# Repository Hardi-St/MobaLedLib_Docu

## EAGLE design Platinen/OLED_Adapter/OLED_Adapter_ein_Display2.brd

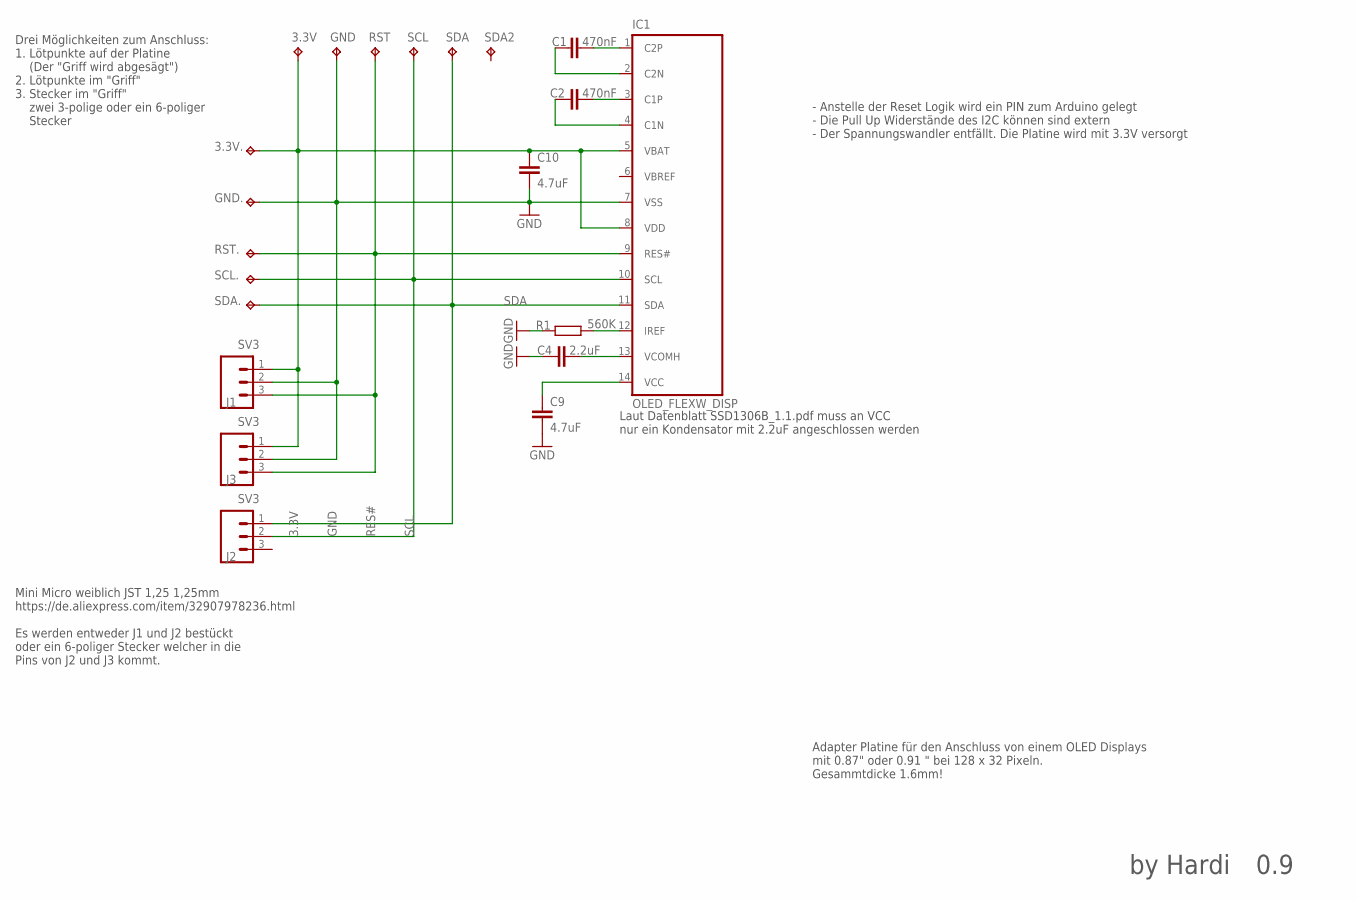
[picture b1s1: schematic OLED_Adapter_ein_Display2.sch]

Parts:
3.3V: 3.3V; TP16SQ
3.3V.: TPTP16SQ; TP16SQ
C1, C2: 470nF; C0603
C4: 2.2uF; C0603
C9, C10: 4.7uF; C0603
GND: GND; TP16R
GND.: TPTP16R; TP16R
IC1: OLED_FLEXW_DISP; OLED_FLEX_W_DISP
J1, J2, J3: SV3; MINI
R1: 560K; R0603
RST: RST; TP16R
RST.: TPTP16R; TP16R
SCL: SCL; TP16R
SCL.: TPTP16R; TP16R
SDA: SDA; TP16R
SDA2: SDA2; TP16R
SDA.: TPTP16R; TP16R

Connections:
3.3V: 3.3V.TP, 3.3V..TP, C10.1, IC1.5 (VBAT), IC1.8 (VDD), J1.1, J3.1
GND: C4.1, C9.2, C10.2, GND.TP, GND..TP, IC1.7 (VSS), J1.2, J3.2, R1.1
unnamed: IC1.12 (IREF), R1.2
unnamed: C1.2, IC1.1 (C2P)
unnamed: C1.1, IC1.2 (C2N)
unnamed: C2.2, IC1.3 (C1P)
unnamed: C2.1, IC1.4 (C1N)
unnamed: C9.1, IC1.14 (VCC)
unnamed: C4.2, IC1.13 (VCOMH)
RES#: IC1.9 (RES#), J1.3, J3.3, RST.TP, RST..TP
SCL: IC1.10 (SCL), J2.2, SCL.TP, SCL..TP
SDA: IC1.11 (SDA), J2.1, SDA.TP, SDA..TP

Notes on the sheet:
Laut Datenblatt SSD1306B_1.1.pdf muss an VCC nur ein Kondensator mit 2.2uF angeschlossen werden
- Anstelle der Reset Logik wird ein PIN zum Arduino gelegt - Die Pull Up Widerstände des I2C können sind extern - Der Spannungswandler entfällt. Die Platine wird mit 3.3V versorgt
Adapter Platine für den Anschluss von einem OLED Displays mit 0.87" oder 0.91 " bei 128 x 32 Pixeln. Gesammtdicke 1.6mm!
0.9
by Hardi
Mini Micro weiblich JST 1,25 1,25mm https://de.aliexpress.com/item/32907978236.html Es werden entweder J1 und J2 bestückt oder ein 6-poliger Stecker welcher in die Pins von J2 und J3 kommt.
Drei Möglichkeiten zum Anschluss: 1. Lötpunkte auf der Platine (Der "Griff wird abgesägt") 2. Lötpunkte im "Griff" 3. Stecker im "Griff" zwei 3-polige oder ein 6-poliger Stecker

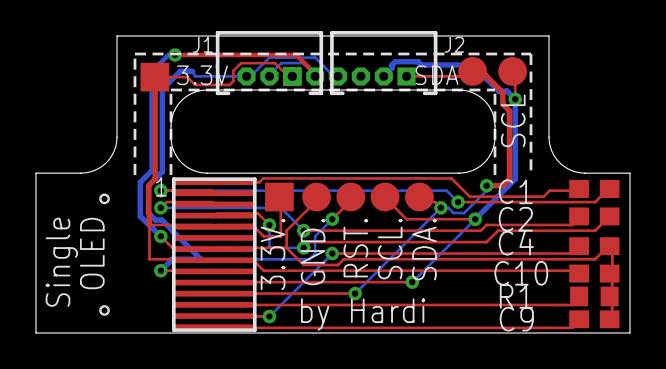
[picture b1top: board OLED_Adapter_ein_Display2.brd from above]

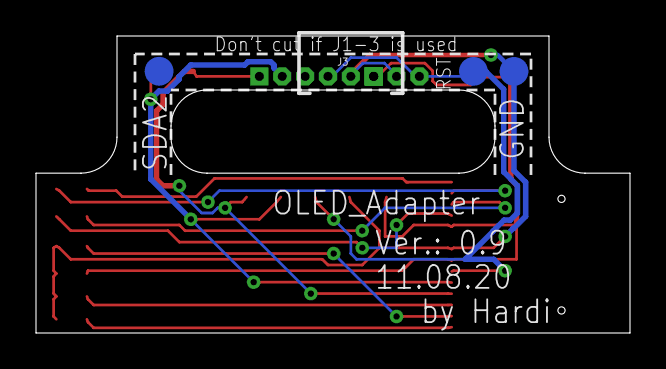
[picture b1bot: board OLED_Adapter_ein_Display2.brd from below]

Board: 2 copper layers, 33.0 x 16.5 mm, 21 parts (4 on the bottom side), 12 nets.

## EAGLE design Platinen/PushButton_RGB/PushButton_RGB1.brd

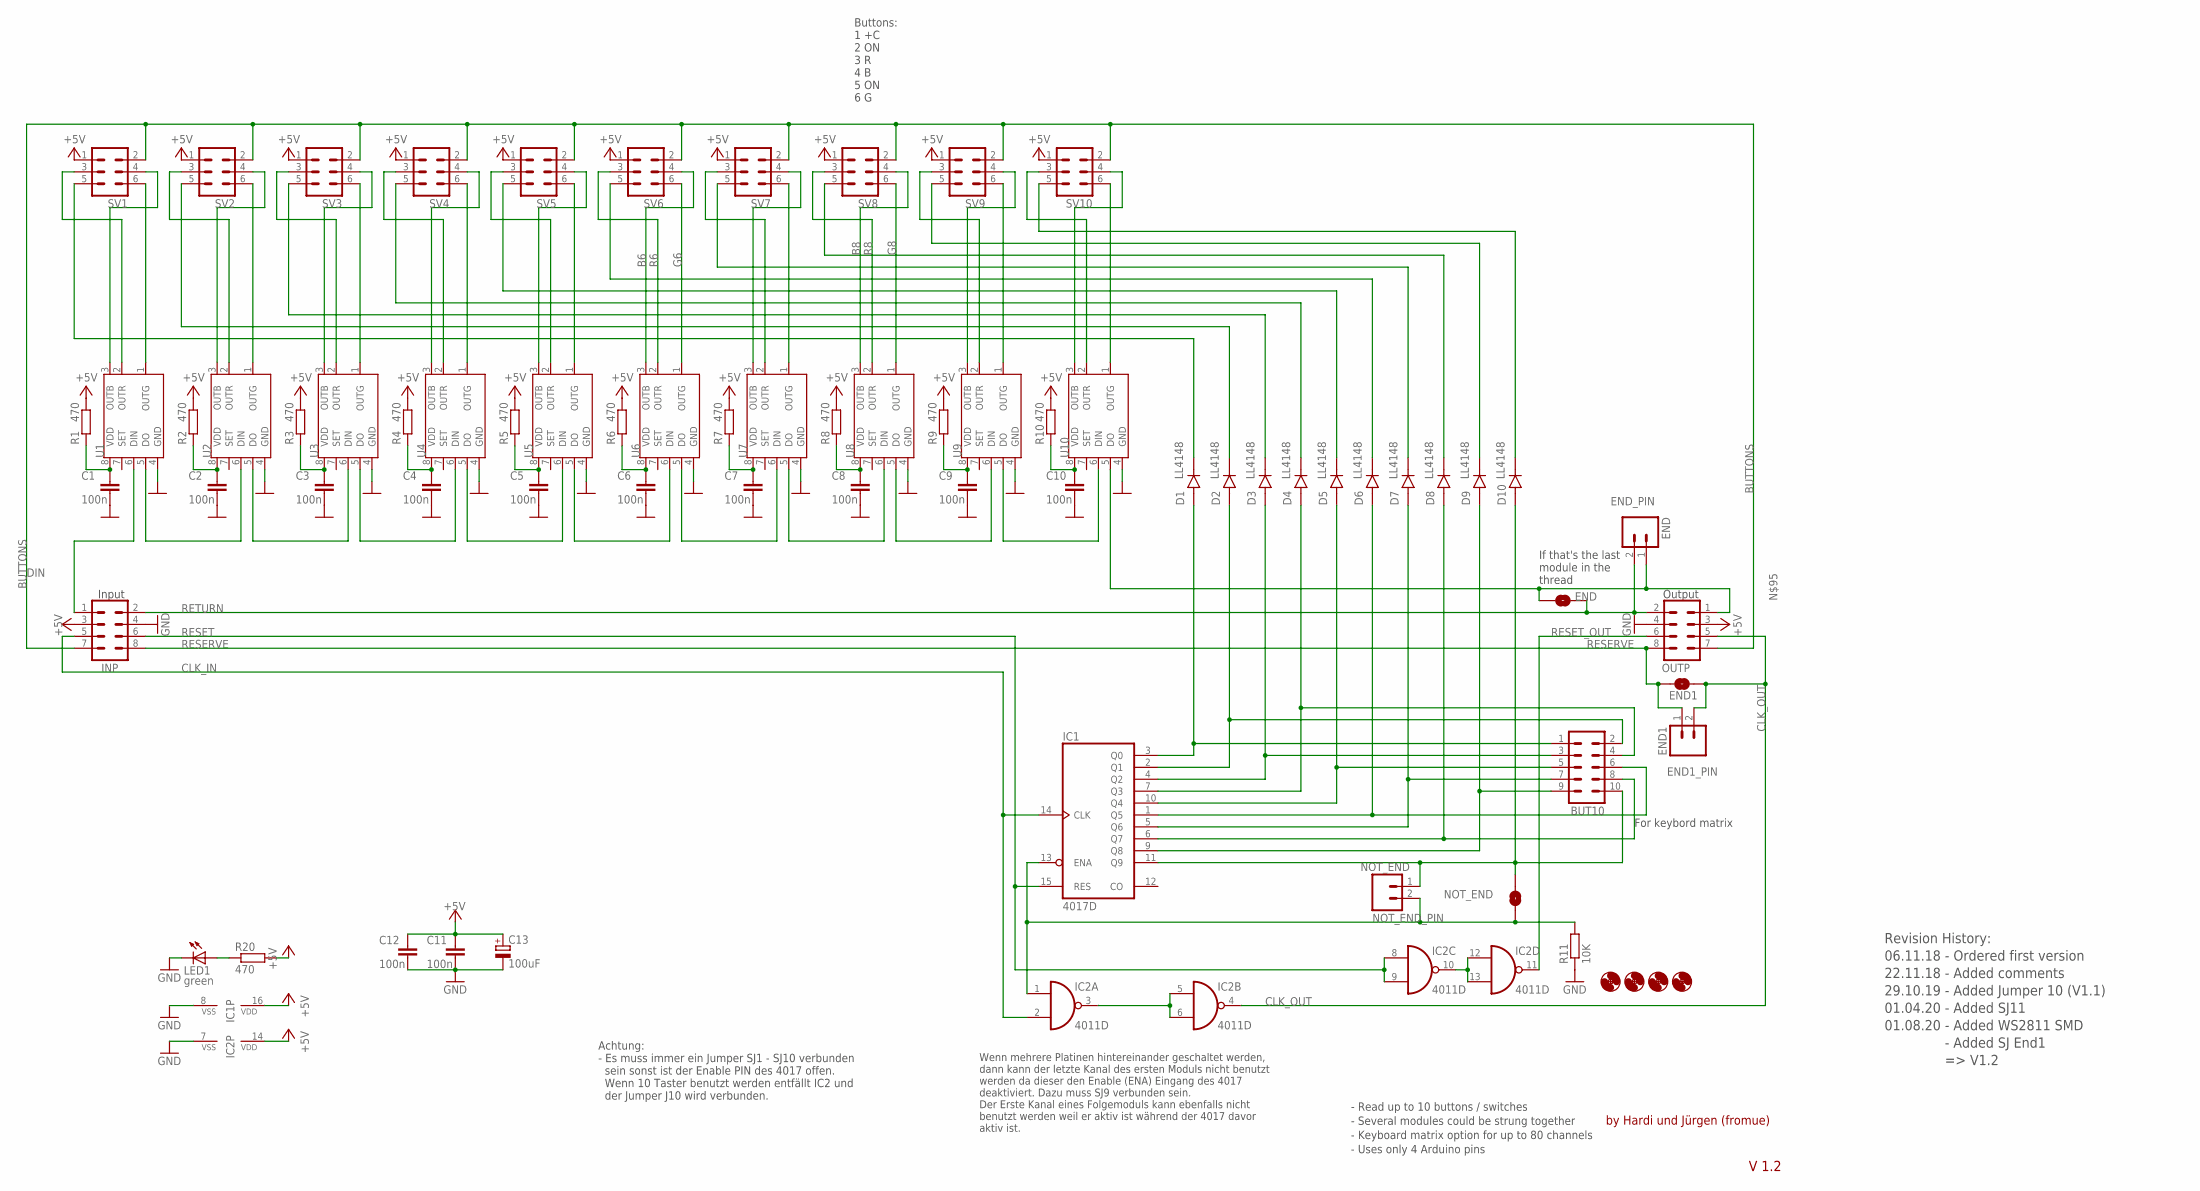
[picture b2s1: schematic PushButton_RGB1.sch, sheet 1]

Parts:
BUT10: CON-HARTING-ML_ML10
C1, C2, C3, C4, C5, C6, C7, C8, C9, C10, C11, C12: 100n; C0603
C13: 100uF; D/7343-31W
D1, D2, D3, D4, D5, D6, D7, D8, D9, D10: LL4148; DIO_LL4148
END, END1: SOLDERJUMPERNO; SJ_2S-NO
END1_PIN: END1; 1X02
END_PIN: END; 1X02
H1, H2, H3: MOUNT-HOLE3.0; 3,0
H4: MOUNT-HOLE2.8; 2,8
IC1: 4017D; SO16
IC2: 4011D; SO14
INP: CON-HARTING-ML_ML08
LED1: green; LED3MM
NOT_END: SOLDERJUMPERNO; SJ_2S-NO
NOT_END_PIN: NOT_END; 1X02
OUTP: CON-HARTING-ML_ML08
R1, R2, R3, R4, R5, R6, R7, R8, R9, R10, R20: 470; R0603
R11: 10K; R0603
SV1, SV2, SV3, SV4, SV5, SV6, SV7, SV8, SV9, SV10: CON-HARTING-ML_ML6
U1, U2, U3, U4, U5, U6, U7, U8, U9, U10: S3PO_MODUL_WS2811_SOUND_MP3-TF-16P_WS2811_AND_ATT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; SOP8

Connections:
+5V: C11.1, C12.1, C13.+, IC1.16 (VDD), IC2.14 (VDD), INP.3, OUTP.3, R1.2, R2.2, R3.2, R4.2, R5.2, R6.2, R7.2, R8.2, R9.2, R10.2, R20.2, SV1.1, SV2.1, SV3.1, SV4.1, SV5.1, SV6.1, SV7.1, SV8.1, SV9.1, SV10.1; also elsewhere on the board
B6: SV6.4, U6.3 (OUTB)
B8: SV8.4, U8.3 (OUTB)
BUTTONS: INP.7, OUTP.7, SV1.2, SV2.2, SV3.2, SV4.2, SV5.2, SV6.2, SV7.2, SV8.2, SV9.2, SV10.2; also elsewhere on the board
CLK_IN: IC1.14 (CLK), IC2.2 (I1), INP.5
CLK_OUT: END1.1, END1_PIN.2, IC2.4 (O), OUTP.5
DIN: INP.1, U1.6 (DIN)
G6: SV6.6, U6.1 (OUTG)
G8: SV8.6, U8.1 (OUTG)
GND: C1.2, C2.2, C3.2, C4.2, C5.2, C6.2, C7.2, C8.2, C9.2, C10.2, C11.2, C12.2, C13.-, IC1.8 (VSS), IC2.7 (VSS), INP.4, LED1.K (C), OUTP.4, R11.1, U1.4 (GND), U2.4 (GND), U3.4 (GND), U4.4 (GND), U5.4 (GND), U6.4 (GND), U7.4 (GND), U8.4 (GND), U9.4 (GND), U10.4 (GND)
unnamed: IC2.3 (O), IC2.5 (I0), IC2.6 (I1)
unnamed: IC1.13 (ENA), IC2.1 (I0), NOT_END.1, NOT_END_PIN.2, R11.2
unnamed: IC2.10 (O), IC2.12 (I0), IC2.13 (I1)
unnamed: BUT10.10, D10.A, IC1.11 (Q9), NOT_END.2, NOT_END_PIN.1
unnamed: C3.1, R3.1, U3.8 (VDD)
unnamed: C6.1, R6.1, U6.8 (VDD)
unnamed: U3.5 (DO), U4.6 (DIN)
unnamed: C4.1, R4.1, U4.8 (VDD)
unnamed: D9.C, SV9.5
unnamed: BUT10.2, D2.A, IC1.2 (Q1)
unnamed: BUT10.3, D3.A, IC1.4 (Q2)
unnamed: BUT10.4, D4.A, IC1.7 (Q3)
unnamed: BUT10.5, D5.A, IC1.10 (Q4)
unnamed: BUT10.6, D6.A, IC1.1 (Q5)
unnamed: BUT10.7, D7.A, IC1.5 (Q6)
unnamed: BUT10.8, D8.A, IC1.6 (Q7)
unnamed: BUT10.9, D9.A, IC1.9 (Q8)
unnamed: SV1.3, U1.2 (OUTR)
unnamed: U4.5 (DO), U5.6 (DIN)
unnamed: LED1.A, R20.1
unnamed: U1.5 (DO), U2.6 (DIN)
unnamed: C5.1, R5.1, U5.8 (VDD)
unnamed: D10.C, SV10.5
unnamed: SV1.4, U1.3 (OUTB)
unnamed: SV1.6, U1.1 (OUTG)
unnamed: BUT10.1, D1.A, IC1.3 (Q0)
unnamed: SV2.4, U2.3 (OUTB)
unnamed: SV2.6, U2.1 (OUTG)
unnamed: SV2.3, U2.2 (OUTR)
unnamed: SV3.4, U3.3 (OUTB)
unnamed: SV3.6, U3.1 (OUTG)
unnamed: SV3.3, U3.2 (OUTR)
unnamed: C1.1, R1.1, U1.8 (VDD)
unnamed: C2.1, R2.1, U2.8 (VDD)
unnamed: U6.5 (DO), U7.6 (DIN)
unnamed: U2.5 (DO), U3.6 (DIN)
unnamed: U5.5 (DO), U6.6 (DIN)
unnamed: C7.1, R7.1, U7.8 (VDD)
unnamed: U7.5 (DO), U8.6 (DIN)
unnamed: C8.1, R8.1, U8.8 (VDD)
unnamed: SV4.4, U4.3 (OUTB)
unnamed: SV4.6, U4.1 (OUTG)
unnamed: U8.5 (DO), U9.6 (DIN)
unnamed: C9.1, R9.1, U9.8 (VDD)
unnamed: SV4.3, U4.2 (OUTR)
unnamed: U9.5 (DO), U10.6 (DIN)
unnamed: C10.1, R10.1, U10.8 (VDD)
unnamed: END.2, END_PIN.1, OUTP.1, U10.5 (DO)
unnamed: SV5.4, U5.3 (OUTB)
unnamed: SV5.6, U5.1 (OUTG)
unnamed: SV5.3, U5.2 (OUTR)
unnamed: SV7.4, U7.3 (OUTB)
unnamed: SV7.6, U7.1 (OUTG)
unnamed: SV7.3, U7.2 (OUTR)
unnamed: SV9.4, U9.3 (OUTB)
unnamed: SV9.6, U9.1 (OUTG)
unnamed: SV9.3, U9.2 (OUTR)
unnamed: SV10.4, U10.3 (OUTB)
unnamed: SV10.6, U10.1 (OUTG)
unnamed: SV10.3, U10.2 (OUTR)
unnamed: D1.C, SV1.5
unnamed: D2.C, SV2.5
unnamed: D3.C, SV3.5
unnamed: D4.C, SV4.5
unnamed: D5.C, SV5.5
unnamed: D6.C, SV6.5
unnamed: D7.C, SV7.5
unnamed: D8.C, SV8.5
R6: SV6.3, U6.2 (OUTR)
R8: SV8.3, U8.2 (OUTR)
RESERVE: END1.2, END1_PIN.1, INP.8, OUTP.8
RESET: IC1.15 (RES), IC2.8 (I0), IC2.9 (I1), INP.6
RESET_OUT: IC2.11 (O), OUTP.6
RETURN: END.1, END_PIN.2, INP.2, OUTP.2

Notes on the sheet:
Input
Output
by Hardi und Jürgen (fromue)
- Read up to 10 buttons / switches - Several modules could be strung together - Keyboard matrix option for up to 80 channels - Uses only 4 Arduino pins
For keybord matrix
If that's the last module in the thread
Achtung: - Es muss immer ein Jumper SJ1 - SJ10 verbunden sein sonst ist der Enable PIN des 4017 offen. Wenn 10 Taster benutzt werden entfällt IC2 und der Jumper J10 wird verbunden.
Wenn mehrere Platinen hintereinander geschaltet werden, dann kann der letzte Kanal des ersten Moduls nicht benutzt werden da dieser den Enable (ENA) Eingang des 4017 deaktiviert. Dazu muss SJ9 verbunden sein. Der Erste Kanal eines Folgemoduls kann ebenfalls nicht benutzt werden weil er aktiv ist wä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
Revision History: 06.11.18 - Ordered first version 22.11.18 - Added comments 29.10.19 - Added Jumper 10 (V1.1) 01.04.20 - Added SJ11 01.08.20 - Added WS2811 SMD - Added SJ End1 => V1.2
V 1.2
Buttons: 1 +C 2 ON 3 R 4 B 5 ON 6 G

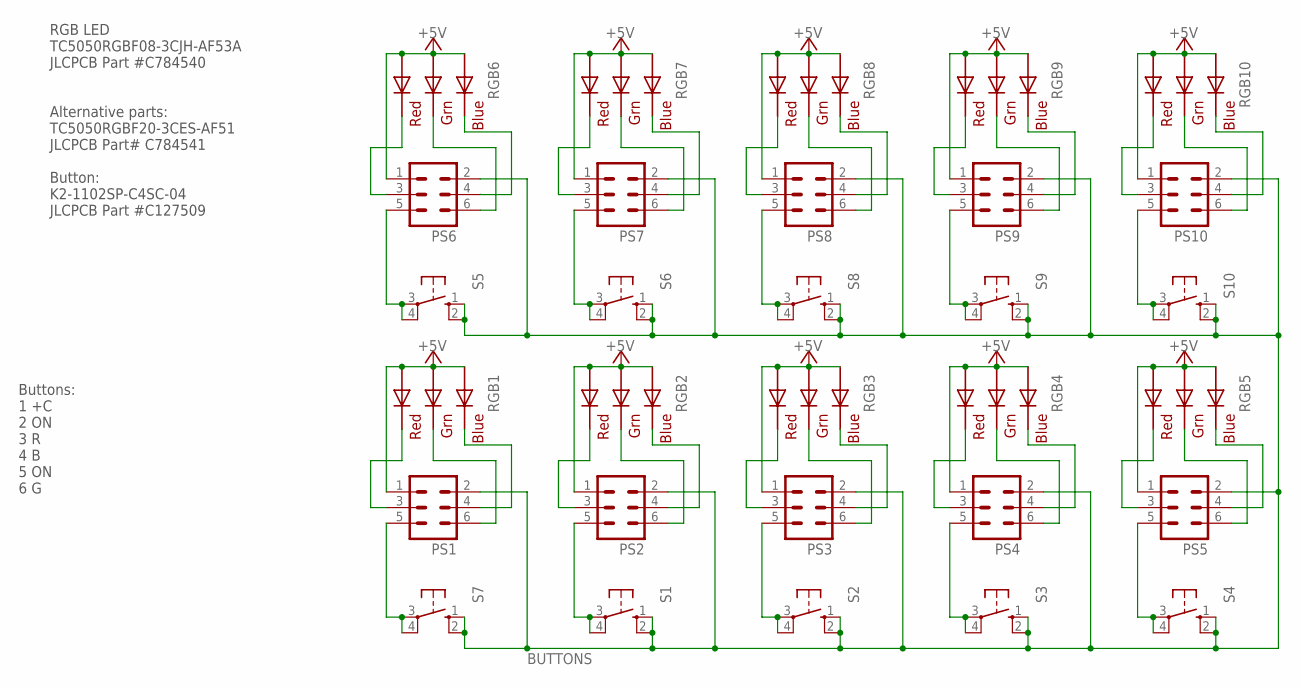
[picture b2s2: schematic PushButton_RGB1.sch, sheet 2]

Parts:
PS1, PS2, PS3, PS4, PS5, PS6, PS7, PS8, PS9, PS10: CON-HARTING-ML_ML6BKL10120958; BKL10120958_MIRROR
RGB1, RGB2, RGB3, RGB4, RGB5, RGB6, RGB7, RGB8, RGB9, RGB10: RGBLED5050
S1, S2, S3, S4, S5, S6, S7, S8, S9, S10: 10-XXB3F-10XX_SMD; B3F-10XX_SMD

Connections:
+5V: PS1.1, PS2.1, PS3.1, PS4.1, PS5.1, PS6.1, PS7.1, PS8.1, PS9.1, PS10.1, RGB1.1 (GREEN_A), RGB1.2 (RED_A), RGB1.3 (BLUE_A), RGB2.1 (GREEN_A), RGB2.2 (RED_A), RGB2.3 (BLUE_A), RGB3.1 (GREEN_A), RGB3.2 (RED_A), RGB3.3 (BLUE_A), RGB4.1 (GREEN_A), RGB4.2 (RED_A), RGB4.3 (BLUE_A), RGB5.1 (GREEN_A), RGB5.2 (RED_A), RGB5.3 (BLUE_A), RGB6.1 (GREEN_A), RGB6.2 (RED_A), RGB6.3 (BLUE_A), RGB7.1 (GREEN_A), RGB7.2 (RED_A), RGB7.3 (BLUE_A), RGB8.1 (GREEN_A), RGB8.2 (RED_A), RGB8.3 (BLUE_A), RGB9.1 (GREEN_A), RGB9.2 (RED_A), RGB9.3 (BLUE_A), RGB10.1 (GREEN_A), RGB10.2 (RED_A), RGB10.3 (BLUE_A); also elsewhere on the board
BUTTONS: PS1.2, PS2.2, PS3.2, PS4.2, PS5.2, PS6.2, PS7.2, PS8.2, PS9.2, PS10.2, S1.1 (S), S1.2 (S1), S2.1 (S), S2.2 (S1), S3.1 (S), S3.2 (S1), S4.1 (S), S4.2 (S1), S5.1 (S), S5.2 (S1), S6.1 (S), S6.2 (S1), S7.1 (S), S7.2 (S1), S8.1 (S), S8.2 (S1), S9.1 (S), S9.2 (S1), S10.1 (S), S10.2 (S1); also elsewhere on the board
B_6: PS6.4, RGB6.4 (BLUE_C)
B_8: PS8.4, RGB8.4 (BLUE_C)
G_6: PS6.6, RGB6.6 (GREEN_C)
G_8: PS8.6, RGB8.6 (GREEN_C)
unnamed: PS1.6, RGB1.6 (GREEN_C)
unnamed: PS1.4, RGB1.4 (BLUE_C)
unnamed: PS1.3, RGB1.5 (RED_C)
unnamed: PS1.5, S7.3, S7.4 (P1)
unnamed: PS2.6, RGB2.6 (GREEN_C)
unnamed: PS2.4, RGB2.4 (BLUE_C)
unnamed: PS2.3, RGB2.5 (RED_C)
unnamed: PS2.5, S1.3, S1.4 (P1)
unnamed: PS3.6, RGB3.6 (GREEN_C)
unnamed: PS3.4, RGB3.4 (BLUE_C)
unnamed: PS3.3, RGB3.5 (RED_C)
unnamed: PS3.5, S2.3, S2.4 (P1)
unnamed: PS4.6, RGB4.6 (GREEN_C)
unnamed: PS4.4, RGB4.4 (BLUE_C)
unnamed: PS4.3, RGB4.5 (RED_C)
unnamed: PS4.5, S3.3, S3.4 (P1)
unnamed: PS5.6, RGB5.6 (GREEN_C)
unnamed: PS5.4, RGB5.4 (BLUE_C)
unnamed: PS5.3, RGB5.5 (RED_C)
unnamed: PS5.5, S4.3, S4.4 (P1)
unnamed: PS6.5, S5.3, S5.4 (P1)
unnamed: PS7.6, RGB7.6 (GREEN_C)
unnamed: PS7.4, RGB7.4 (BLUE_C)
unnamed: PS7.3, RGB7.5 (RED_C)
unnamed: PS7.5, S6.3, S6.4 (P1)
unnamed: PS8.5, S8.3, S8.4 (P1)
unnamed: PS9.6, RGB9.6 (GREEN_C)
unnamed: PS9.4, RGB9.4 (BLUE_C)
unnamed: PS9.3, RGB9.5 (RED_C)
unnamed: PS9.5, S9.3, S9.4 (P1)
unnamed: PS10.6, RGB10.6 (GREEN_C)
unnamed: PS10.4, RGB10.4 (BLUE_C)
unnamed: PS10.3, RGB10.5 (RED_C)
unnamed: PS10.5, S10.3, S10.4 (P1)
R_6: PS6.3, RGB6.5 (RED_C)
R_8: PS8.3, RGB8.5 (RED_C)

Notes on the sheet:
Buttons: 1 +C 2 ON 3 R 4 B 5 ON 6 G
RGB LED TC5050RGBF08-3CJH-AF53A JLCPCB Part #C784540 Alternative parts: TC5050RGBF20-3CES-AF51 JLCPCB Part# C784541 Button: K2-1102SP-C4SC-04 JLCPCB Part #C127509

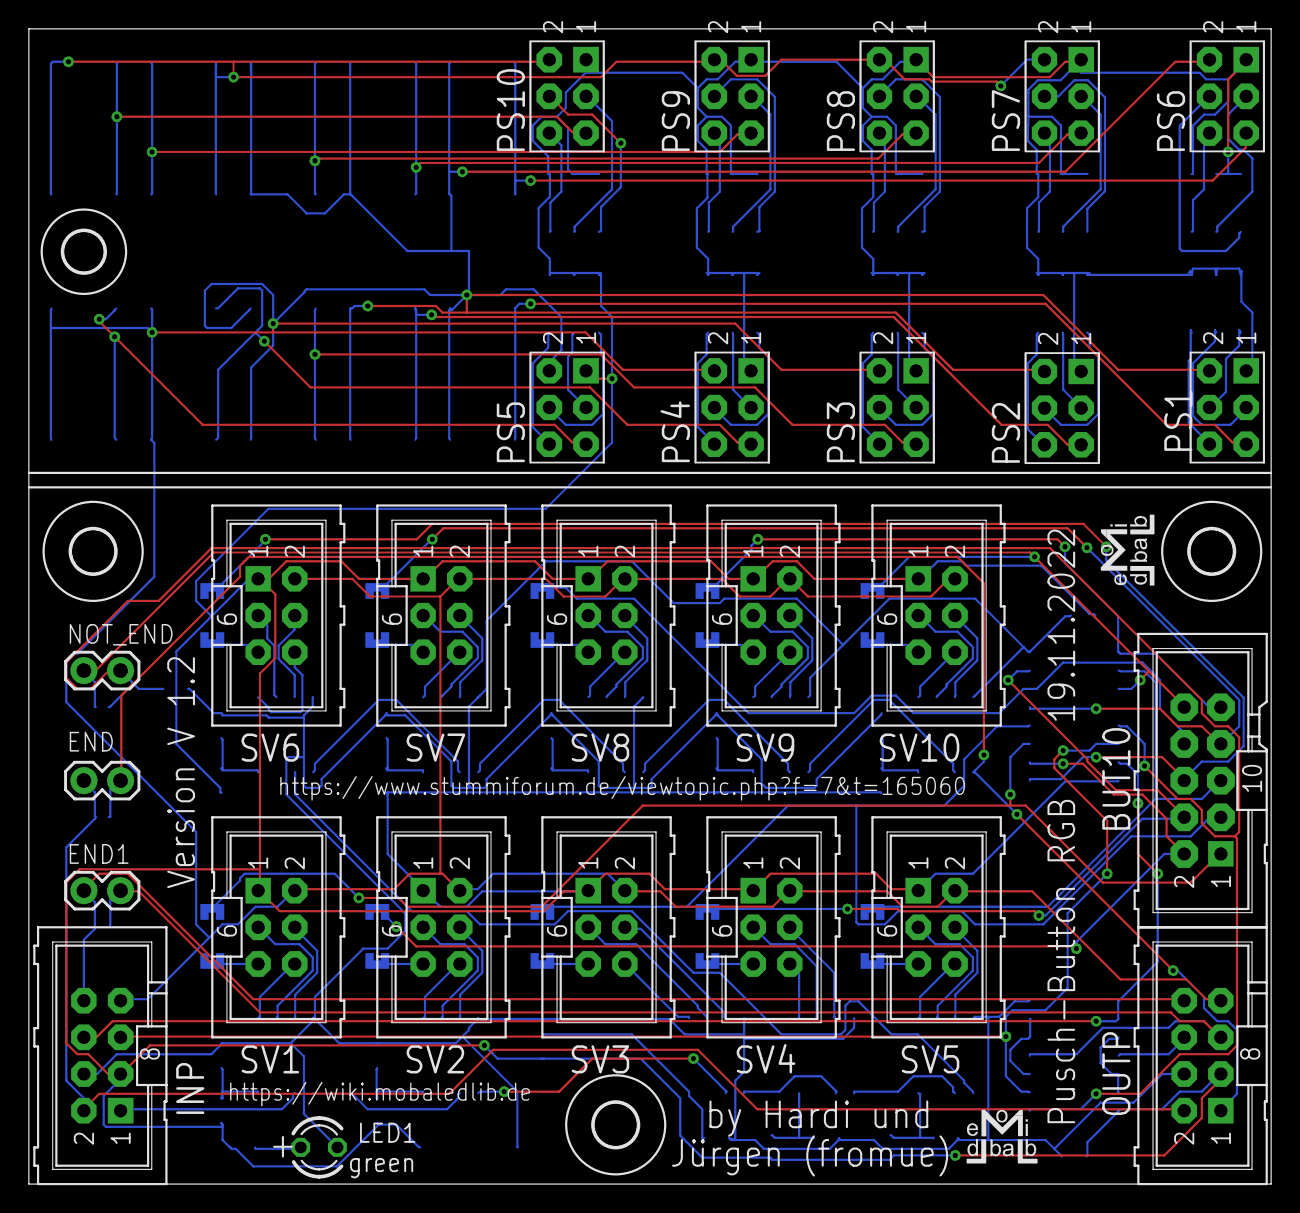
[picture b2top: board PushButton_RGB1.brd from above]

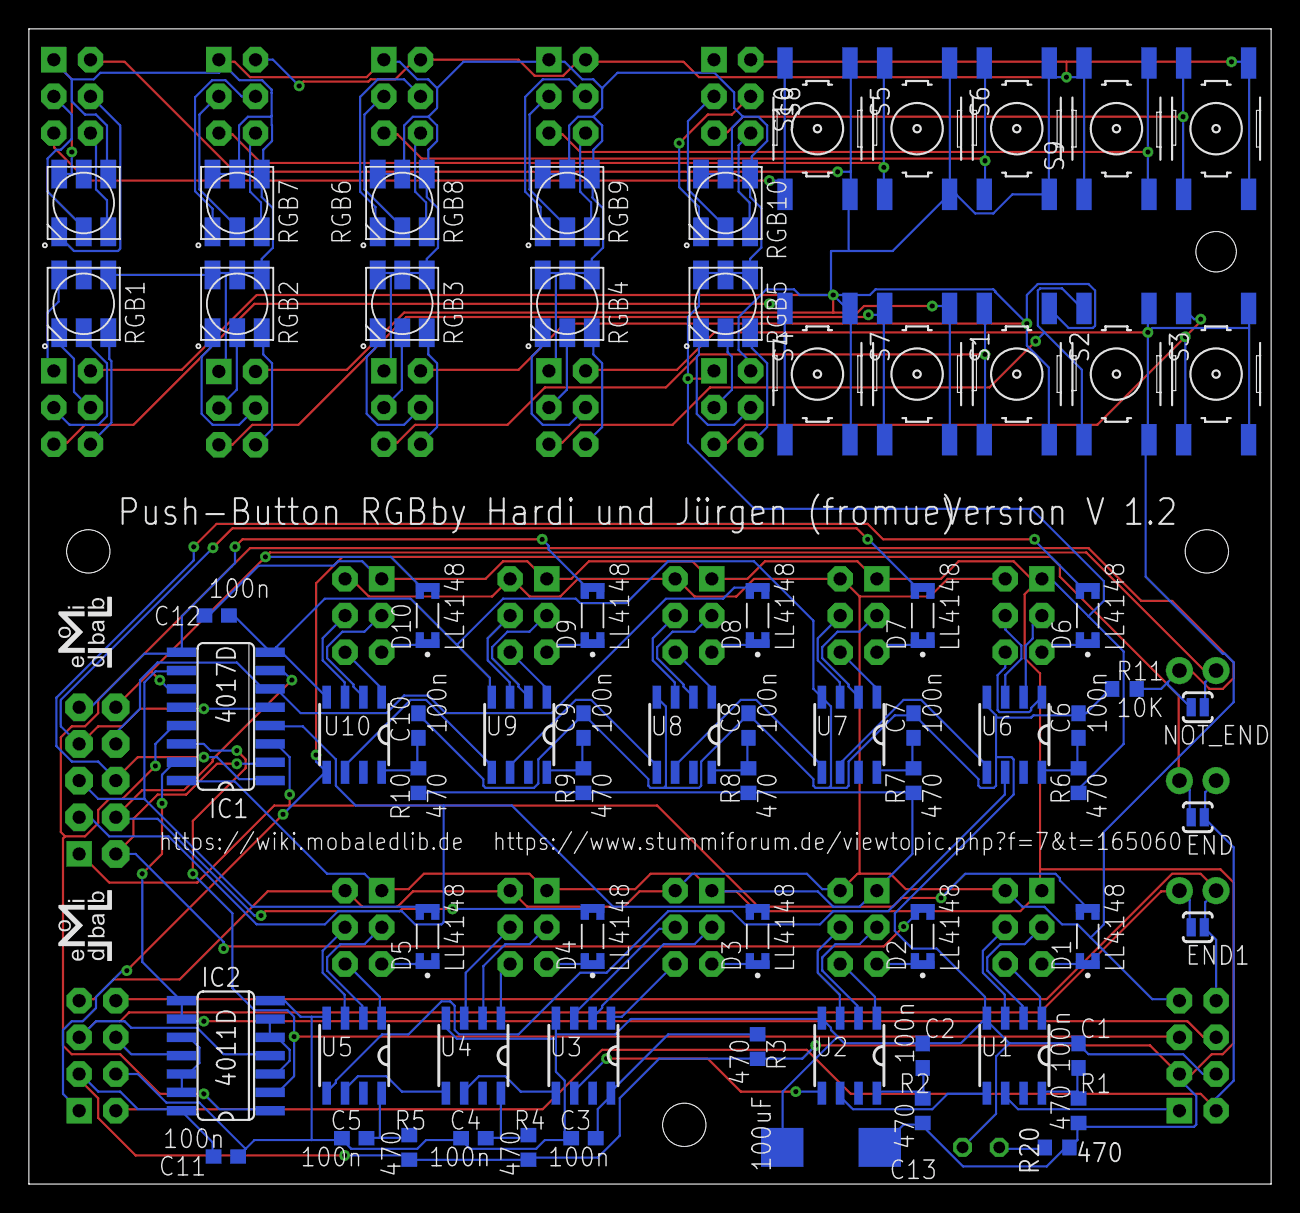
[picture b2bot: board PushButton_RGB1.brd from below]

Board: 2 copper layers, 86.0 x 80.0 mm, 101 parts (70 on the bottom side), 124 nets.

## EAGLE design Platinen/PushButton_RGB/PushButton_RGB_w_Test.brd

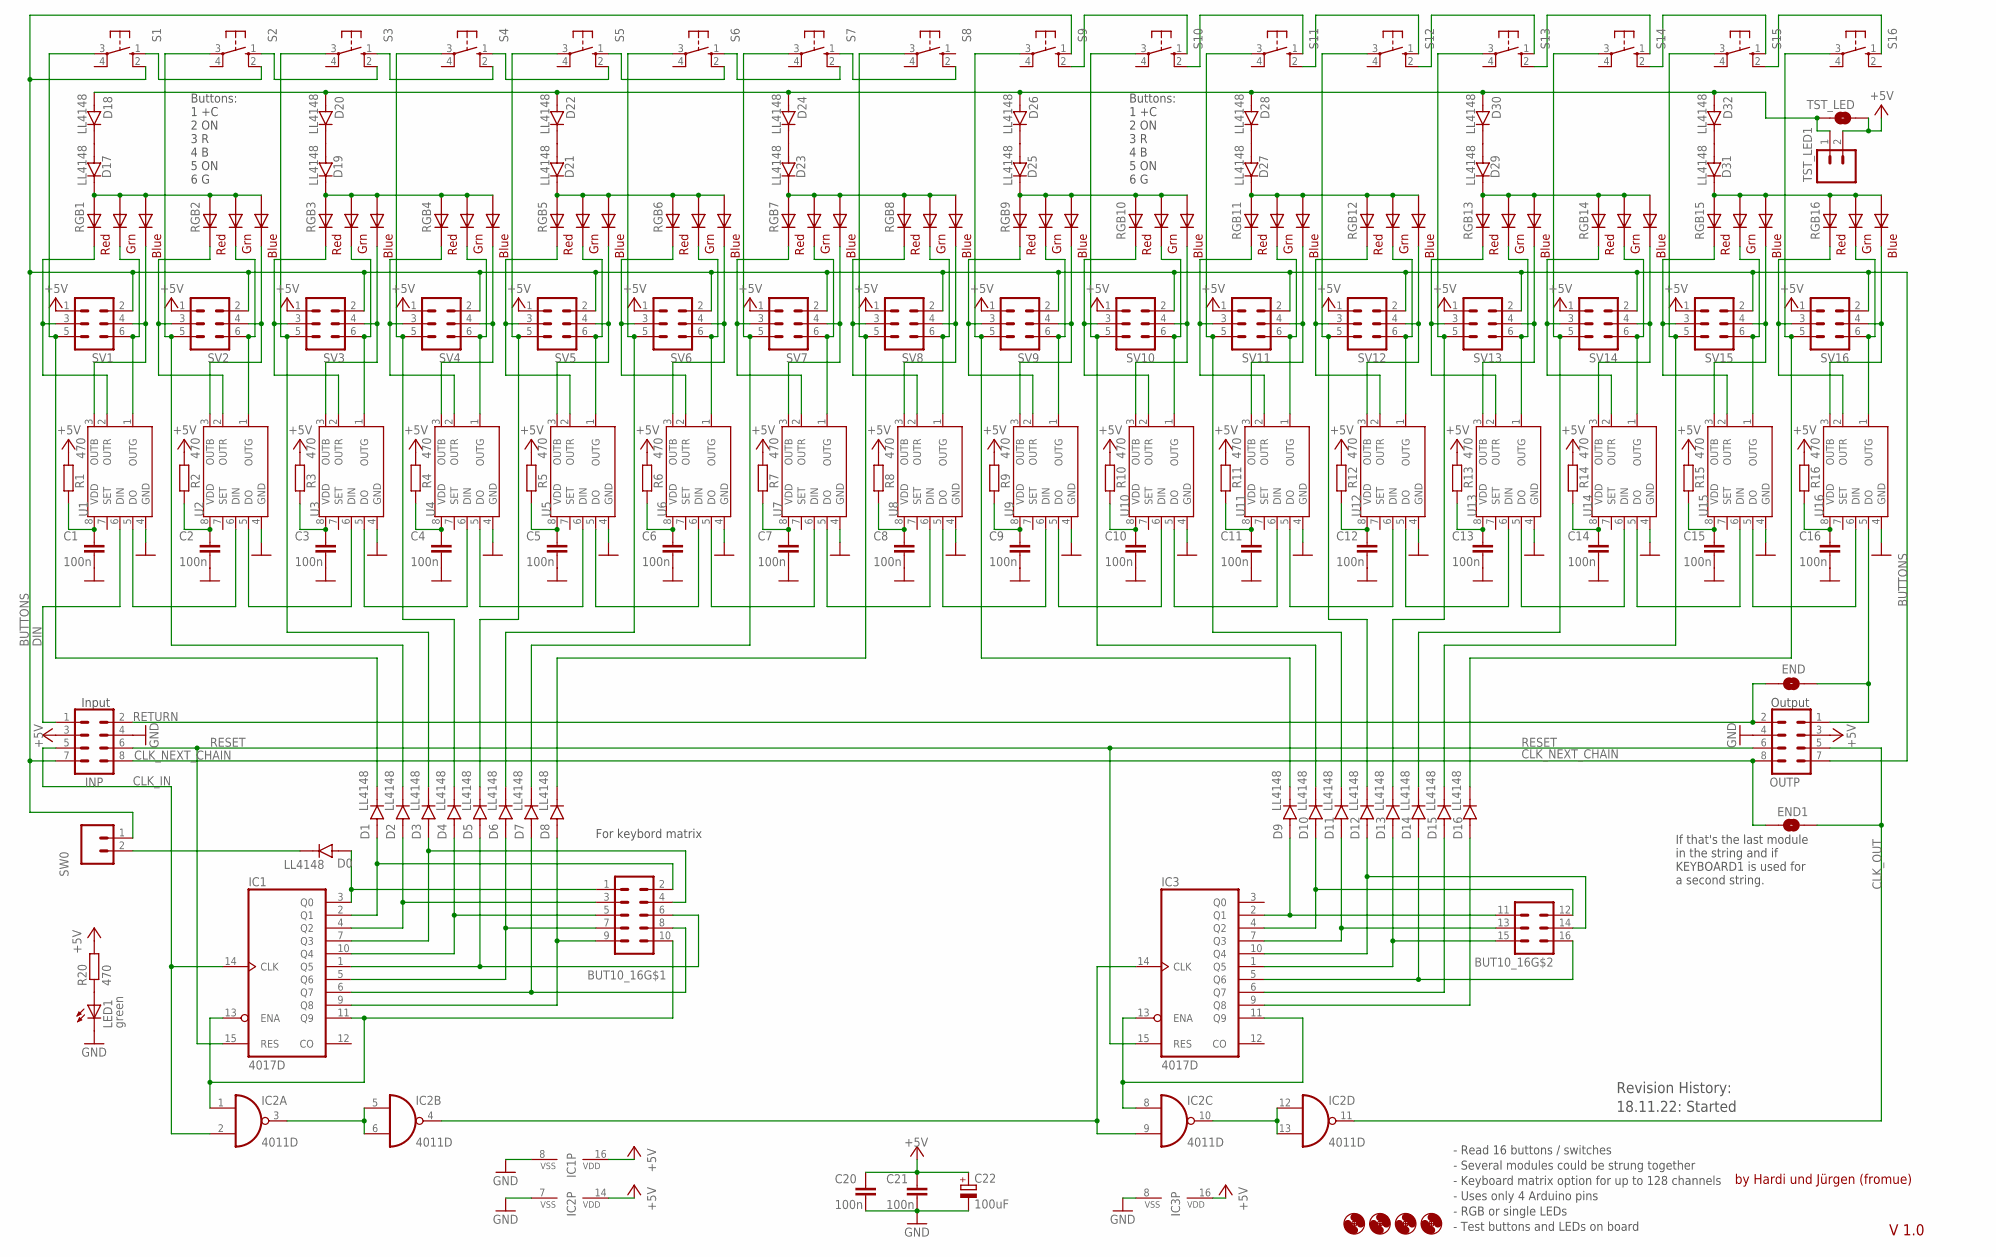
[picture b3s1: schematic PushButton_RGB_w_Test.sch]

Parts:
BUT10_16: CON-HARTING-ML_ML16-2; CON-HARTING-ML_ML16
C1, C2, C3, C4, C5, C6, C7, C8, C9, C10, C11, C12, C13, C14, C15, C16, C20, C21: 100n; C0603
C22: 100uF; B/3528-21R
D0, D1, D2, D3, D4, D5, D6, D7, D8, D9, D10, D11, D12, D13, D14, D15, D16, D17, D18, D19, D20, D21, D22, D23, D24, D25, D26, D27, D28, D29, D30, D31, D32: LL4148; DIO_LL4148
END, END1: SOLDERJUMPERNO; SJ_2S-NO
H1, H2, H3, H4: MOUNT-HOLE3.0; 3,0
IC1, IC3: 4017D; SO16
IC2: 4011D; SO14
INP: CON-HARTING-ML_ML08
LED1: green; CHIPLED_0805
OUTP: CON-HARTING-ML_ML08
R1, R2, R3, R4, R5, R6, R7, R8, R9, R10, R11, R12, R13, R14, R15, R16, R20: 470; R0603
RGB1, RGB2, RGB3, RGB4, RGB5, RGB6, RGB7, RGB8, RGB9, RGB10, RGB11, RGB12, RGB13, RGB14, RGB15, RGB16: RGBLED5050
S1, S2, S3, S4, S5, S6, S7, S8, S9, S10, S11, S12, S13, S14, S15, S16: 10-XXB3F-10XX_SMD; B3F-10XX_SMD
SV1, SV2, SV3, SV4, SV5, SV6, SV7, SV8, SV9, SV10, SV11, SV12, SV13, SV14, SV15, SV16: CON-HARTING-ML_ML6
SW0: M02PTH; 1X02
TST_LED: SOLDERJUMPERNO; SJ_2S-NO
TST_LED1: Tst_LED; 1X02
U1, U2, U3, U4, U5, U6, U7, U8, U9, U10, U11, U12, U13, U14, U15, U16: S3PO_MODUL_WS2811_SOUND_MP3-TF-16P_WS2811_AND_ATT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; SOP8

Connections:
+5V: C20.1, C21.1, C22.+, IC1.16 (VDD), IC2.14 (VDD), IC3.16 (VDD), INP.3, OUTP.3, R1.2, R2.2, R3.2, R4.2, R5.2, R6.2, R7.2, R8.2, R9.2, R10.2, R11.2, R12.2, R13.2, R14.2, R15.2, R16.2, R20.2, SV1.1, SV2.1, SV3.1, SV4.1, SV5.1, SV6.1, SV7.1, SV8.1, SV9.1, SV10.1, SV11.1, SV12.1, SV13.1, SV14.1, SV15.1, SV16.1, TST_LED.1, TST_LED1.2
BUTTONS: INP.7, OUTP.7, S1.2 (S1), S9.1 (S), SV1.2, SV2.2, SV3.2, SV4.2, SV5.2, SV6.2, SV7.2, SV8.2, SV9.2, SV10.2, SV11.2, SV12.2, SV13.2, SV14.2, SV15.2, SV16.2, SW0.1
CLK_IN: IC1.14 (CLK), IC2.2 (I1), INP.5
CLK_NEXT_CHAIN: END1.2, INP.8, OUTP.8
CLK_OUT: END1.1, IC2.11 (O), OUTP.5
DIN: INP.1, U1.6 (DIN)
GND: C1.2, C2.2, C3.2, C4.2, C5.2, C6.2, C7.2, C8.2, C9.2, C10.2, C11.2, C12.2, C13.2, C14.2, C15.2, C16.2, C20.2, C21.2, C22.-, IC1.8 (VSS), IC2.7 (VSS), IC3.8 (VSS), INP.4, LED1.C, OUTP.4, U1.4 (GND), U2.4 (GND), U3.4 (GND), U4.4 (GND), U5.4 (GND), U6.4 (GND), U7.4 (GND), U8.4 (GND), U9.4 (GND), U10.4 (GND), U11.4 (GND), U12.4 (GND), U13.4 (GND), U14.4 (GND), U15.4 (GND), U16.4 (GND)
unnamed: IC2.3 (O), IC2.5 (I0), IC2.6 (I1)
unnamed: U10.5 (DO), U11.6 (DIN)
unnamed: BUT10_16.11 (1), D9.A, IC3.2 (Q1)
unnamed: U1.5 (DO), U2.6 (DIN)
unnamed: BUT10_16.10, IC1.11 (Q9), IC1.13 (ENA), IC2.1 (I0)
unnamed: C2.1, R2.1, U2.8 (VDD)
unnamed: D0.C, SW0.2
unnamed: RGB2.4 (BLUE_C), SV2.4, U2.3 (OUTB)
unnamed: RGB2.6 (GREEN_C), SV2.6, U2.1 (OUTG)
unnamed: RGB2.5 (RED_C), SV2.3, U2.2 (OUTR)
unnamed: BUT10_16.2, D1.A, IC1.2 (Q1)
unnamed: BUT10_16.3, D2.A, IC1.4 (Q2)
unnamed: BUT10_16.4, D3.A, IC1.7 (Q3)
unnamed: BUT10_16.5, D4.A, IC1.10 (Q4)
unnamed: BUT10_16.6, D5.A, IC1.1 (Q5)
unnamed: BUT10_16.7, D6.A, IC1.5 (Q6)
unnamed: BUT10_16.8, D7.A, IC1.6 (Q7)
unnamed: BUT10_16.9, D8.A, IC1.9 (Q8)
unnamed: RGB1.5 (RED_C), SV1.3, U1.2 (OUTR)
unnamed: D18.A, D20.A, D22.A, D24.A, D26.A, D28.A, D30.A, D32.A, TST_LED.2, TST_LED1.1
unnamed: LED1.A, R20.1
unnamed: D17.A, D18.C
unnamed: S1.1 (S), S2.2 (S1)
unnamed: U2.5 (DO), U3.6 (DIN)
unnamed: D10.C, S10.3, SV10.5
unnamed: RGB1.4 (BLUE_C), SV1.4, U1.3 (OUTB)
unnamed: RGB1.6 (GREEN_C), SV1.6, U1.1 (OUTG)
unnamed: BUT10_16.12 (2), D10.A, IC3.4 (Q2)
unnamed: BUT10_16.13 (3), D11.A, IC3.7 (Q3)
unnamed: BUT10_16.14 (4), D12.A, IC3.10 (Q4)
unnamed: BUT10_16.15 (5), D13.A, IC3.1 (Q5)
unnamed: S2.1 (S), S3.2 (S1)
unnamed: BUT10_16.16 (6), D14.A, IC3.5 (Q6)
unnamed: S3.1 (S), S4.2 (S1)
unnamed: BUT10_16.1, D0.A, IC1.3 (Q0)
unnamed: D15.A, IC3.6 (Q7)
unnamed: D16.A, IC3.9 (Q8)
unnamed: IC2.10 (O), IC2.12 (I0), IC2.13 (I1)
unnamed: D19.A, D20.C
unnamed: IC2.8 (I0), IC3.11 (Q9), IC3.13 (ENA)
unnamed: IC2.4 (O), IC2.9 (I1), IC3.14 (CLK)
unnamed: S4.1 (S), S5.2 (S1)
unnamed: D21.A, D22.C
unnamed: S5.1 (S), S6.2 (S1)
unnamed: C3.1, R3.1, U3.8 (VDD)
unnamed: D3.C, S3.3, SV3.5
unnamed: RGB3.4 (BLUE_C), SV3.4, U3.3 (OUTB)
unnamed: RGB3.6 (GREEN_C), SV3.6, U3.1 (OUTG)
unnamed: RGB3.5 (RED_C), SV3.3, U3.2 (OUTR)
unnamed: D19.C, RGB3.1 (GREEN_A), RGB3.2 (RED_A), RGB3.3 (BLUE_A), RGB4.1 (GREEN_A), RGB4.2 (RED_A), RGB4.3 (BLUE_A)
unnamed: S6.1 (S), S7.2 (S1)
unnamed: U3.5 (DO), U4.6 (DIN)
unnamed: D23.A, D24.C
unnamed: S7.1 (S), S8.2 (S1)
unnamed: D25.A, D26.C
unnamed: C4.1, R4.1, U4.8 (VDD)
unnamed: S9.2 (S1), S10.1 (S)
unnamed: RGB4.4 (BLUE_C), SV4.4, U4.3 (OUTB)
unnamed: RGB4.6 (GREEN_C), SV4.6, U4.1 (OUTG)
unnamed: RGB4.5 (RED_C), SV4.3, U4.2 (OUTR)
unnamed: S10.2 (S1), S11.1 (S)
unnamed: S11.2 (S1), S12.1 (S)
unnamed: U4.5 (DO), U5.6 (DIN)
unnamed: D27.A, D28.C
unnamed: S12.2 (S1), S13.1 (S)
unnamed: D29.A, D30.C
unnamed: C5.1, R5.1, U5.8 (VDD)
unnamed: S13.2 (S1), S14.1 (S)
unnamed: RGB5.4 (BLUE_C), SV5.4, U5.3 (OUTB)
unnamed: RGB5.6 (GREEN_C), SV5.6, U5.1 (OUTG)
unnamed: RGB5.5 (RED_C), SV5.3, U5.2 (OUTR)
unnamed: D21.C, RGB5.1 (GREEN_A), RGB5.2 (RED_A), RGB5.3 (BLUE_A), RGB6.1 (GREEN_A), RGB6.2 (RED_A), RGB6.3 (BLUE_A)
unnamed: S14.2 (S1), S15.1 (S)
unnamed: D31.A, D32.C
unnamed: U5.5 (DO), U6.6 (DIN)
unnamed: C1.1, R1.1, U1.8 (VDD)
unnamed: S15.2 (S1), S16.1 (S)
unnamed: C6.1, R6.1, U6.8 (VDD)
unnamed: RGB6.4 (BLUE_C), SV6.4, U6.3 (OUTB)
unnamed: RGB6.6 (GREEN_C), SV6.6, U6.1 (OUTG)
unnamed: RGB6.5 (RED_C), SV6.3, U6.2 (OUTR)
unnamed: U6.5 (DO), U7.6 (DIN)
unnamed: C7.1, R7.1, U7.8 (VDD)
unnamed: C10.1, R10.1, U10.8 (VDD)
unnamed: RGB7.4 (BLUE_C), SV7.4, U7.3 (OUTB)
unnamed: RGB7.6 (GREEN_C), SV7.6, U7.1 (OUTG)
unnamed: RGB7.5 (RED_C), SV7.3, U7.2 (OUTR)
unnamed: D23.C, RGB7.1 (GREEN_A), RGB7.2 (RED_A), RGB7.3 (BLUE_A), RGB8.1 (GREEN_A), RGB8.2 (RED_A), RGB8.3 (BLUE_A)
unnamed: U7.5 (DO), U8.6 (DIN)
unnamed: C8.1, R8.1, U8.8 (VDD)
unnamed: RGB8.4 (BLUE_C), SV8.4, U8.3 (OUTB)
unnamed: RGB8.6 (GREEN_C), SV8.6, U8.1 (OUTG)
unnamed: RGB8.5 (RED_C), SV8.3, U8.2 (OUTR)
unnamed: U8.5 (DO), U9.6 (DIN)
unnamed: RGB10.4 (BLUE_C), SV10.4, U10.3 (OUTB)
unnamed: RGB10.6 (GREEN_C), SV10.6, U10.1 (OUTG)
unnamed: RGB10.5 (RED_C), SV10.3, U10.2 (OUTR)
unnamed: C12.1, R12.1, U12.8 (VDD)
unnamed: D1.C, S1.3, SV1.5
unnamed: D2.C, S2.3, SV2.5
unnamed: D4.C, S4.3, SV4.5
unnamed: D5.C, S5.3, SV5.5
unnamed: D6.C, S6.3, SV6.5
unnamed: D7.C, S7.3, SV7.5
unnamed: D8.C, S8.3, SV8.5
unnamed: C9.1, R9.1, U9.8 (VDD)
unnamed: D17.C, RGB1.1 (GREEN_A), RGB1.2 (RED_A), RGB1.3 (BLUE_A), RGB2.1 (GREEN_A), RGB2.2 (RED_A), RGB2.3 (BLUE_A)
unnamed: D12.C, S12.3, SV12.5
unnamed: D9.C, S9.3, SV9.5
unnamed: RGB12.4 (BLUE_C), SV12.4, U12.3 (OUTB)
unnamed: RGB9.4 (BLUE_C), SV9.4, U9.3 (OUTB)
unnamed: RGB9.6 (GREEN_C), SV9.6, U9.1 (OUTG)
unnamed: RGB9.5 (RED_C), SV9.3, U9.2 (OUTR)
unnamed: D25.C, RGB9.1 (GREEN_A), RGB9.2 (RED_A), RGB9.3 (BLUE_A), RGB10.1 (GREEN_A), RGB10.2 (RED_A), RGB10.3 (BLUE_A)
unnamed: U9.5 (DO), U10.6 (DIN)
unnamed: C11.1, R11.1, U11.8 (VDD)
unnamed: D11.C, S11.3, SV11.5
unnamed: RGB11.4 (BLUE_C), SV11.4, U11.3 (OUTB)
unnamed: RGB11.6 (GREEN_C), SV11.6, U11.1 (OUTG)
unnamed: RGB11.5 (RED_C), SV11.3, U11.2 (OUTR)
unnamed: U11.5 (DO), U12.6 (DIN)
unnamed: RGB12.6 (GREEN_C), SV12.6, U12.1 (OUTG)
unnamed: RGB12.5 (RED_C), SV12.3, U12.2 (OUTR)
unnamed: D27.C, RGB11.1 (GREEN_A), RGB11.2 (RED_A), RGB11.3 (BLUE_A), RGB12.1 (GREEN_A), RGB12.2 (RED_A), RGB12.3 (BLUE_A)
unnamed: U12.5 (DO), U13.6 (DIN)
unnamed: C13.1, R13.1, U13.8 (VDD)
unnamed: D13.C, S13.3, SV13.5
unnamed: RGB13.4 (BLUE_C), SV13.4, U13.3 (OUTB)
unnamed: RGB13.6 (GREEN_C), SV13.6, U13.1 (OUTG)
unnamed: RGB13.5 (RED_C), SV13.3, U13.2 (OUTR)
unnamed: D29.C, RGB13.1 (GREEN_A), RGB13.2 (RED_A), RGB13.3 (BLUE_A), RGB14.1 (GREEN_A), RGB14.2 (RED_A), RGB14.3 (BLUE_A)
unnamed: U13.5 (DO), U14.6 (DIN)
unnamed: C14.1, R14.1, U14.8 (VDD)
unnamed: D14.C, S14.3, SV14.5
unnamed: RGB14.4 (BLUE_C), SV14.4, U14.3 (OUTB)
unnamed: RGB14.6 (GREEN_C), SV14.6, U14.1 (OUTG)
unnamed: RGB14.5 (RED_C), SV14.3, U14.2 (OUTR)
unnamed: U14.5 (DO), U15.6 (DIN)
unnamed: C15.1, R15.1, U15.8 (VDD)
unnamed: D15.C, S15.3, SV15.5
unnamed: RGB15.4 (BLUE_C), SV15.4, U15.3 (OUTB)
unnamed: RGB15.6 (GREEN_C), SV15.6, U15.1 (OUTG)
unnamed: RGB15.5 (RED_C), SV15.3, U15.2 (OUTR)
unnamed: D31.C, RGB15.1 (GREEN_A), RGB15.2 (RED_A), RGB15.3 (BLUE_A), RGB16.1 (GREEN_A), RGB16.2 (RED_A), RGB16.3 (BLUE_A)
unnamed: U15.5 (DO), U16.6 (DIN)
unnamed: C16.1, R16.1, U16.8 (VDD)
unnamed: D16.C, S16.3, SV16.5
unnamed: RGB16.4 (BLUE_C), SV16.4, U16.3 (OUTB)
unnamed: RGB16.6 (GREEN_C), SV16.6, U16.1 (OUTG)
unnamed: RGB16.5 (RED_C), SV16.3, U16.2 (OUTR)
unnamed: END.2, OUTP.1, U16.5 (DO)
RESET: IC1.15 (RES), IC3.15 (RES), INP.6, OUTP.6
RETURN: END.1, INP.2, OUTP.2

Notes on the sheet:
Input
Output
by Hardi und Jürgen (fromue)
- Read 16 buttons / switches - Several modules could be strung together - Keyboard matrix option for up to 128 channels - Uses only 4 Arduino pins - RGB or single LEDs - Test buttons and LEDs on board
For keybord matrix
If that's the last module in the string and if KEYBOARD1 is used for a second string.
Revision History: 18.11.22: Started
V 1.0
Buttons: 1 +C 2 ON 3 R 4 B 5 ON 6 G

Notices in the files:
parts and their libraries:
SparkFun-Retired: Licensing:Creative Commons ShareAlike 4.0 International - https://creativecommons.org/licenses/by-sa/4.0
